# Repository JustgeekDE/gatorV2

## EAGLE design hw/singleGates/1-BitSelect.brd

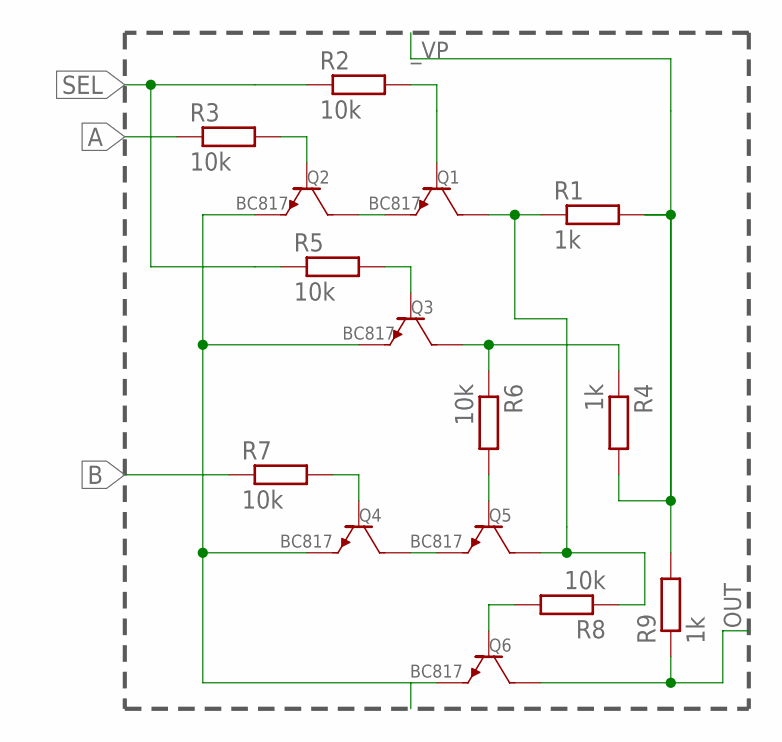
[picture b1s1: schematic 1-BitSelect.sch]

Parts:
Q1, Q2, Q3, Q4, Q5, Q6: BC817; SOT23
R1, R4, R9: 1k; R0603
R2, R3, R5, R6, R7, R8: 10k; R0603

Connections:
A: R3.1
B: R7.1
I-S2: Q3.P$3 (COLLECTOR), R4.1, R6.1
unnamed: Q1.P$1 (BASE), R2.2
unnamed: Q2.P$1 (BASE), R3.2
unnamed: Q1.P$2 (EMITTER), Q2.P$3 (COLLECTOR)
unnamed: Q5.P$1 (BASE), R6.2
unnamed: Q4.P$1 (BASE), R7.2
unnamed: Q4.P$3 (COLLECTOR), Q5.P$2 (EMITTER)
unnamed: Q6.P$1 (BASE), R8.2
unnamed: Q3.P$1 (BASE), R5.2
OUT: Q6.P$3 (COLLECTOR), R9.1
SEL: R2.1, R5.1
SEL_INT1: Q1.P$3 (COLLECTOR), Q5.P$3 (COLLECTOR), R1.1, R8.1
_VN: Q2.P$2 (EMITTER), Q3.P$2 (EMITTER), Q4.P$2 (EMITTER), Q6.P$2 (EMITTER)
_VP: R1.2, R4.2, R9.2

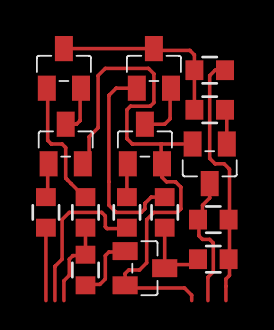
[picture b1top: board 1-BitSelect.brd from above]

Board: 2 copper layers, 15 parts (0 on the bottom side), 14 nets.

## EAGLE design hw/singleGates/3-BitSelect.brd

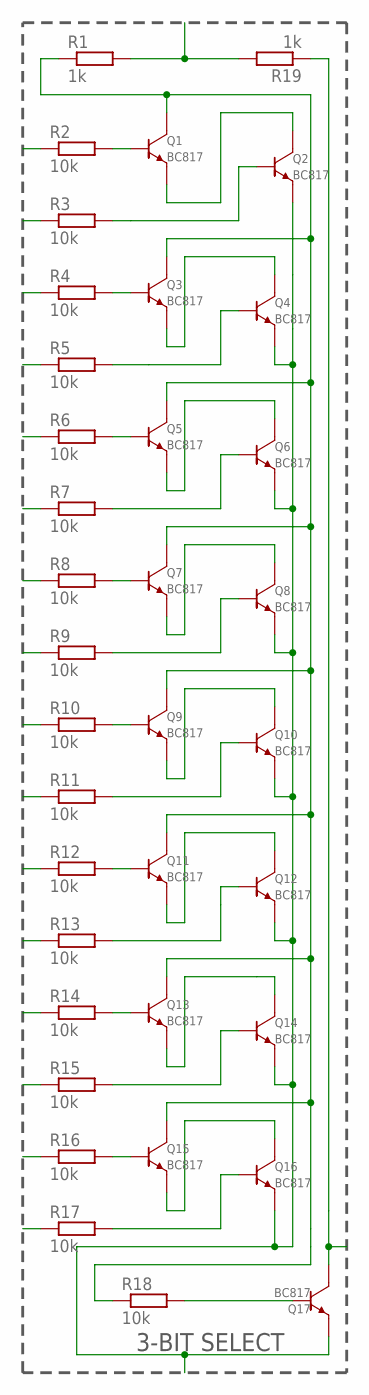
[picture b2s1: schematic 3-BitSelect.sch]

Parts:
Q1, Q2, Q3, Q4, Q5, Q6, Q7, Q8, Q9, Q10, Q11, Q12, Q13, Q14, Q15, Q16, Q17: BC817; SOT23
R1, R19: 1k; R0603
R2, R3, R4, R5, R6, R7, R8, R9, R10, R11, R12, R13, R14, R15, R16, R17, R18: 10k; R0603

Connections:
I1: R3.1
I2: R5.1
I3: R7.1
I4: R9.1
I5: R11.1
I6: R13.1
I7: R15.1
I8: R17.1
unnamed: Q1.P$1 (BASE), R2.2
unnamed: Q2.P$1 (BASE), R3.2
unnamed: Q1.P$2 (EMITTER), Q2.P$3 (COLLECTOR)
unnamed: Q3.P$1 (BASE), R4.2
unnamed: Q4.P$1 (BASE), R5.2
unnamed: Q3.P$2 (EMITTER), Q4.P$3 (COLLECTOR)
unnamed: Q5.P$1 (BASE), R6.2
unnamed: Q6.P$1 (BASE), R7.2
unnamed: Q5.P$2 (EMITTER), Q6.P$3 (COLLECTOR)
unnamed: Q7.P$1 (BASE), R8.2
unnamed: Q8.P$1 (BASE), R9.2
unnamed: Q7.P$2 (EMITTER), Q8.P$3 (COLLECTOR)
unnamed: Q9.P$1 (BASE), R10.2
unnamed: Q10.P$1 (BASE), R11.2
unnamed: Q9.P$2 (EMITTER), Q10.P$3 (COLLECTOR)
unnamed: Q11.P$1 (BASE), R12.2
unnamed: Q12.P$1 (BASE), R13.2
unnamed: Q11.P$2 (EMITTER), Q12.P$3 (COLLECTOR)
unnamed: Q13.P$1 (BASE), R14.2
unnamed: Q14.P$1 (BASE), R15.2
unnamed: Q13.P$2 (EMITTER), Q14.P$3 (COLLECTOR)
unnamed: Q15.P$1 (BASE), R16.2
unnamed: Q16.P$1 (BASE), R17.2
unnamed: Q15.P$2 (EMITTER), Q16.P$3 (COLLECTOR)
unnamed: Q17.P$1 (BASE), R18.2
OUT: Q17.P$3 (COLLECTOR), R19.1
S1: R2.1
S2: R4.1
S3: R6.1
S4: R8.1
S5: R10.1
S6: R12.1
S7: R14.1
S8: R16.1
SEL_INT: Q1.P$3 (COLLECTOR), Q3.P$3 (COLLECTOR), Q5.P$3 (COLLECTOR), Q7.P$3 (COLLECTOR), Q9.P$3 (COLLECTOR), Q11.P$3 (COLLECTOR), Q13.P$3 (COLLECTOR), Q15.P$3 (COLLECTOR), R1.1, R18.1
_VN: Q2.P$2 (EMITTER), Q4.P$2 (EMITTER), Q6.P$2 (EMITTER), Q8.P$2 (EMITTER), Q10.P$2 (EMITTER), Q12.P$2 (EMITTER), Q14.P$2 (EMITTER), Q16.P$2 (EMITTER), Q17.P$2 (EMITTER)
_VP: R1.2, R19.2

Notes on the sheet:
3-BIT SELECT

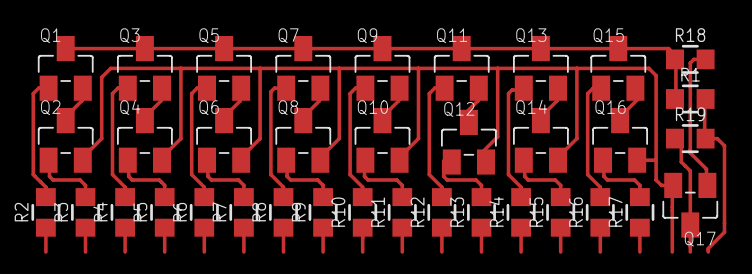
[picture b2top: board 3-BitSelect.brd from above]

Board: 2 copper layers, 36 parts (0 on the bottom side), 29 nets.

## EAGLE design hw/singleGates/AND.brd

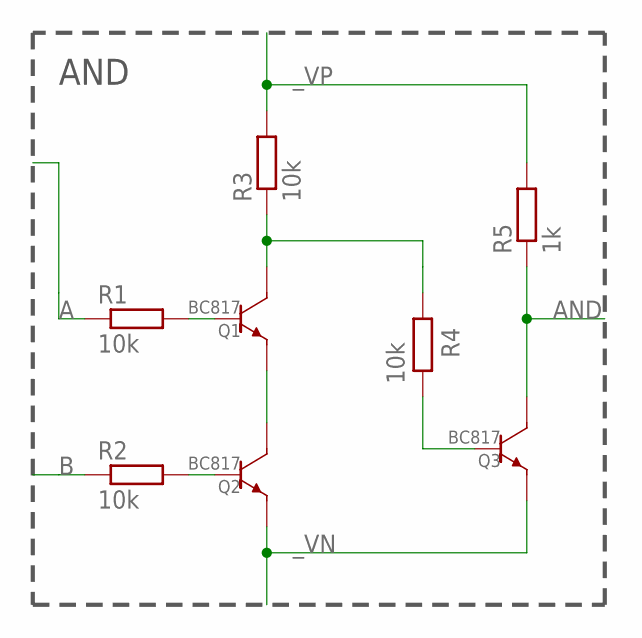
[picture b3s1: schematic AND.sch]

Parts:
Q1, Q2, Q3: BC817; SOT23
R1, R2, R3, R4: 10k; R0603
R5: 1k; R0603

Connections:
A: R1.1
AND: Q3.P$3 (COLLECTOR), R5.1
B: R2.1
unnamed: Q1.P$1 (BASE), R1.2
unnamed: Q1.P$3 (COLLECTOR), R3.1, R4.2
unnamed: Q2.P$1 (BASE), R2.2
unnamed: Q1.P$2 (EMITTER), Q2.P$3 (COLLECTOR)
unnamed: Q3.P$1 (BASE), R4.1
_VN: Q2.P$2 (EMITTER), Q3.P$2 (EMITTER)
_VP: R3.2, R5.2

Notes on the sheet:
AND

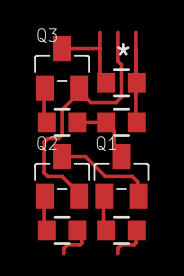
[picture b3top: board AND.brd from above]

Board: 2 copper layers, 8 parts (0 on the bottom side), 8 nets.
